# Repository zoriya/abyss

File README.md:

# Abyss

A 32 key split keyboard with a low pinky column.

## Components

| Count | Part name        | Size/Remark |
| :---: | :--------------  | :------ |
|   2x  | [Seeed Xiao nRF54L15 - mcu](https://www.seeedstudio.com/XIAO-nRF54L15-p-6493.html) | |
|   2x  | [1208YD - reset button](https://fr.aliexpress.com/item/1005003938985112.html?spm=a2g0o.order_list.order_list_main.5.21ef1802F8o6h5&gatewayAdapt=glo2fra) | 6x6x7mm |
|   2x  | [401030 Li-Po Battery](https://www.ebay.com/itm/171812433827) | 4x10x30mm |
|   2x  | [SM02B-SRSS-TB - battery connector](https://www.jst-mfg.com/product/pdf/eng/eSH.pdf) | |
|  32x  | choc switch | i use [sunsets](https://lowprokb.ca/products/sunset-tactile-choc-switches) |
|  30x  | 1u choc keycaps | i use [pom](https://splitkb.com/products/moergo-pom-mbk-profile-keycaps?variant=42898367152387) |
|   2x  | 1.5u choc keycaps | i use [pom](https://splitkb.com/products/moergo-pom-mbk-profile-keycaps?variant=42898363121923) |
|  32x  | [hotswap chock sockets](https://chosfox.com/products/kailh-choc-switch-1350-hot-swap-sockets?_pos=1&_sid=94423b5bb&_ss=r) | |
|  32x  | diodes | |
|  16x  | magnets | [20x8x1.5mm](https://www.amazon.fr/dp/B0DDCVJTG8?th=1) |
|   4x  | m2 screws | 4/6/8mm |
|   4x  | m2 standoff | [<5mm wide, 6mm height](https://www.aliexpress.us/item/3256804230166399.html?spm=a2g0o.productlist.main.6.3a56Op21Op215V&algo_pvid=0788da77-fa40-49b3-9d72-f4cf68a2b90f&algo_exp_id=0788da77-fa40-49b3-9d72-f4cf68a2b90f-5&pdp_ext_f=%7B%22order%22%3A%22229%22%2C%22eval%22%3A%221%22%7D&pdp_npi=6%40dis%21USD%212.35%210.99%21%21%212.35%210.99%21%40211b655217567292930196247e11b4%2112000029108517137%21sea%21US%210%21ABX%211%210%21n_tag%3A-29910%3Bd%3A8c8b81cd%3Bm03_new_user%3A-29895%3BpisId%3A5000000174221208&curPageLogUid=uw39hgxJul2o&utparam-url=scene%3Asearch%7Cquery_from%3A%7Cx_object_id%3A1005004416481151%7C_p_origin_prod%3A#nav-description)|

## Info

Case dimensions:
 - height: 10.5mm -> 1.6mm (pcb) + 3.1mm (hotswap socket) + 5.5mm (choc size on top of the pcb)
 - length: 115.38mm
 - width: 96.25mm

Transport case dimesions:
- height: 30mm (2x2mm for enclosure, 2x10.5mm for keyboard, 5mm in middle for keycaps + gap)
- length: 124.35mm
-  width: 105.25mm

## Keymap

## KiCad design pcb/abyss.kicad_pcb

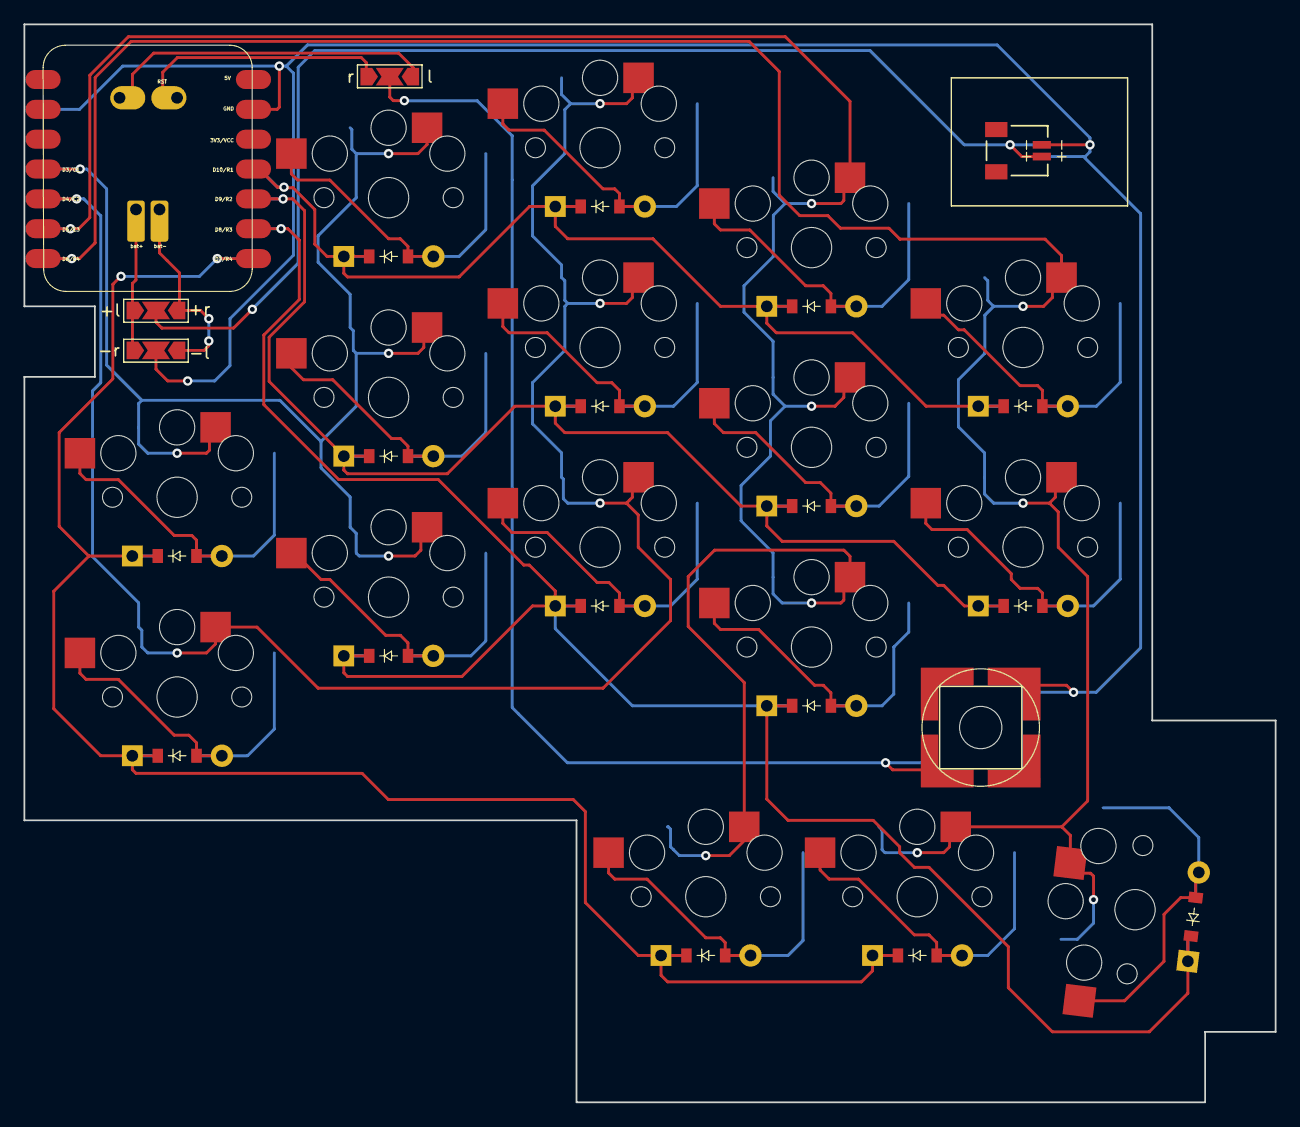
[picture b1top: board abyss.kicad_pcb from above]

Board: 2 copper layers, 106.5 x 91.8 mm, 32 parts (0 on the bottom side), 24 nets.

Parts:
D1, D2, D3, D4, D5, D6, D7, D8, D9, D10, D11, D12, D13, D14, D15, D16: ComboDiode
S1, S2, S3, S4, S5, S6, S7, S8, S9, S10, S11, S12, S13, S14, S15, S16: PG1350

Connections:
C1: S2.1, S3.1, S4.1, S5.1
C2: S1.1, S6.1, S7.1, S8.1
C3: S9.1, S10.1, S11.1, S14.1
C4: S12.1, S13.1, S15.1, S16.1
R1: D5.1, D8.1, D11.1, D13.1
R2: D4.1, D7.1, D10.1, D12.1
R3: D3.1, D6.1, D9.1, D16.1
R4: D1.1, D2.1, D14.1, D15.1
home_cluster: D15.2, S15.2
index_bottom: D9.2, S9.2
index_home: D10.2, S10.2
index_top: D11.2, S11.2
inner_bottom: D12.2, S12.2
inner_home: D13.2, S13.2
left_cluster: D14.2, S14.2
middle_bottom: D6.2, S6.2
middle_home: D7.2, S7.2
middle_top: D8.2, S8.2
pinky_bottom: D1.2, S1.2
pinky_home: D2.2, S2.2
right_cluster: D16.2, S16.2
ring_bottom: D3.2, S3.2
ring_home: D4.2, S4.2
ring_top: D5.2, S5.2

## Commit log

2024-01-31 Add outlines
2024-01-31 Add proper 1.5u thumb size
2024-01-31 Use higher padding
2024-02-04 Use square outlines and start pcb
2024-02-06 Add infused kim footprints
2024-02-06 Fix oled pos
2024-02-06 Add reset and power switch
2024-02-06 Rotate reset/power switches
2024-02-07 Add keys and oled routing hints
2024-02-07 Fix extra column in routing
2024-02-14 Fix nets
2024-02-15 Remove nice view footprint
2024-02-19 Add battery jst and cleanup layout
2024-02-19 Move jst connector at the top
2024-02-19 Add case walls
2024-02-20 Create plate
2024-02-20 Add mounting holes on the pcb
2024-02-20 Create top case
2024-02-20 Add mounting holes for the plate on the pcb
2024-02-20 Route pcb
2024-02-28 Finish pcb routing
2024-02-28 Add plate pcb
2024-03-17 Plate diffs
2024-04-07 Case wip
2024-04-07 Init zmk config
2024-04-07 Set github action working directory
2024-04-07 Override default config files names
2024-04-07 Create abyss shield
2024-04-07 Create basic keymap
2024-04-07 Move zmk config to root
2024-04-07 Add zmk metadata file
2024-04-07 Move boards to config foldre
2024-04-07 Move metadata file to boards/shield folder
2024-04-07 Add shield keymap
2024-04-07 Move back to config folder :(
2024-04-07 fix typo
2024-04-07 Remove zephyr module
2024-04-07 oups
2024-04-07 Rename dtsi to overlay
2024-04-07 Fix keymap
2024-04-07 Fix keymap codes
2024-04-08 Fix some keys
2024-04-10 Cleanup layout ascii art
2024-04-10 Add homerow mods
2024-04-10 Add missing keys as combo
2024-04-10 Add keymap draw tools
2024-04-10 Add home and end combo
2024-04-10 Add parenthesis combo
2024-04-10 Add dash/underscore combo
2024-04-10 Add symbols layer
2024-04-10 Fix bracket combo
2024-04-10 Add keymap.svg
2024-04-11 Add directions keys and esc combo
2024-04-11 Fix bscp and layout.svg
2024-04-11 Fix up/down swapped and space delay
2024-04-13 Add another z combo
2024-04-13 Add a : combo
2024-04-13 Add enter combo
2024-04-13 Add bluethooth bindings
2024-04-13 Change deep sleep timing to 20min
2024-04-13 Add media keys
2024-04-13 Add capswords
2024-04-13 Use play instead of playpause btn
2024-04-13 Use playpause instead of play
2024-04-15 Remove combo/mod require delay
2024-04-15 Fix weird nav keys
2024-04-15 Add a specefic enter key for shift enter
2024-04-30 Bind shift instead of enter on the left thumb
2024-04-30 Fix shift keycode
2024-04-30 Use urob fork to disable capsword after modifiers
2024-04-30 Add reset firmware to ci
2024-04-30 Use n0 on the two right thumbs
2024-05-22 Mark kscan as wakeup-source
2024-05-22 Use eager debouncing
2024-05-22 Enable split battery reporting
2024-07-14 Init FreeCad case project
2024-08-23 Define left/right keys instead of using them twice
2024-08-23 Add reset button
2024-08-23 Add reset on both sides
2024-08-23 Use my fork of zmk
2024-08-23 Fix reset
2024-09-12 Case top start
2024-09-12 Add mc pin holes
2024-09-13 Add walls and usb hole
2024-09-13 Add fillets
2024-09-13 Add inner fillets
2024-09-13 Add screw holes
2024-09-13 wip fix sketches
2024-09-13 fix sketches part 2
2024-09-14 wip wall part2
2024-09-14 Restart case and make clean sketches
2024-09-14 Correct sketches placements
2024-09-14 Create bottom lid
2024-09-14 Add screw holes in bottom lid
2024-09-15 things
2024-09-15 Make better bottom
2024-09-15 Better tolerances
2024-09-16 Add walls
2024-09-16 Add inner walls
2024-09-16 Correct inner wall
2024-09-16 Add screw holes in wall (part 1)
2024-09-17 Allign screw holes
2024-09-17 Fillet bottom walls
2024-09-17 Add key holes
2024-09-18 Add mc hole
2024-09-18 Better mc distances
2024-09-18 Add inner keys hole sketch
2024-09-18 Finish key hole sketch
2024-09-18 Add key hole
2024-09-18 Fix flipped constraints
2024-09-18 Fix recompute issues
2024-09-18 Add missing screw holes
2024-09-18 Add usb hole sketch
2024-09-18 Add usb hole
2024-09-19 Add nut holes
2024-09-19 Remove corners for nut holes
2024-09-22 Add feet holes
2024-09-23 Add feets
2024-09-23 Remove old case tries
2024-09-27 Draft feets
2024-09-27 Make nut slot smaller
2024-09-27 Update orchidee.svg to real svg
2024-09-27 Remake lid
2024-09-27 Properly allign screw holes
2024-09-29 Add nut shape in holes
2024-09-29 new orchid
2024-09-29 Add the orchid on the surface
2024-09-29 Add tolerence for feets
2024-09-29 Fix spacing
2024-09-30 Remove bottom ledge & increment lit tolerence
2024-09-30 Reduce wall height
2024-09-30 Increment feet tolerences & height
2024-10-01 Fix feet magnet pocket height
2024-10-01 Widen screw holes
2024-10-01 Reset orchid drawing (source from flora)
2024-10-01 Scale orchid by 1.1 & flip horizontally
2024-10-01 Scale orchid path
2024-10-03 Add nut slot covers
2024-10-03 Update orchid
2024-10-03 Add slots for nuts
2024-10-06 Fix lid tolerences and rework nut slot
2024-10-14 Add keep mod shift for arrows
2024-10-14 Add hold shift on capsword
2024-10-15 Fix arrows
2024-12-06 Add keymap-drawer to shell.nix
2024-12-06 Add require delay to homerow mods
2024-12-06 Swap capsword w/ sticky lshift
2024-12-06 Configure sticky shift to be good
2025-01-19 Remove useless z combo
2025-02-09 Add shift on left hand
2025-02-09 Update keymap drawer
2025-02-09 Fix caps_word not working due to zmkfirmware/zmk#834
2025-02-09 Disable sticky shift lazy
2025-02-25 Handle caps word cancellation
2025-04-13 Start rework
2025-04-13 Add xiao footprint
2025-04-13 Fix mcu position
2025-04-13 Reverse battery connector
2025-04-13 Remove pcb
2025-04-13 Init pcb & add mcu
2025-04-14 Add power switch footprint
2025-04-17 Restart case
2025-04-18 Re-rework case
2025-04-18 Move case2 to case
2025-04-18 Add key cutout
2025-04-18 Try to fix distances
2025-04-18 Fix thumb key
2025-04-18 Add battery slot
2025-08-17 Fix case height
2025-08-17 Fix tolerences
2025-08-18 Add socket holes
2025-08-18 Move usb hole to bottom
2025-08-18 wip: Create transport case
2025-08-18 Add honeycomb for case
2025-08-18 Open case in two
2025-08-18 Add case stands
2025-08-18 Start feet slips
2025-08-19 Add feet slips on case
2025-08-19 Pad case to fit keyboard correctly
2025-08-20 Fix socket hole
2025-08-20 Add m2 holes to fix bottom & top
2025-08-20 Make case more square
2025-08-20 Add case side stands
2025-08-20 Fix pcb size
2025-08-20 Fix transport case cuttout
2025-08-20 Transport case gap
2025-08-20 Reinit pcb
2025-08-25 wip: Add mc footprint
2025-08-25 wip: Fix case angle
2025-08-26 Fix case angle
2025-08-26 Cleanup case
2025-08-26 Use 4mm walls for transport case
2025-08-26 wip: Better case
2025-08-26 wip: Pcb
2025-08-26 Fix angles
2025-08-26 Cleanup fillets
2025-08-26 Add magnet holes
2025-08-26 Add reset button hole
2025-08-26 Add reset button to pcb
2025-08-26 Add through hole for reset btn
2025-08-26 Add counterbore for m2
2025-08-26 wip: Add m2 holes in pcb
2025-08-30 Use ergogen and keymap-drawer from nixpkgs now that they are packaged
2025-08-30 Cleanup footprints
2025-08-30 Fix row/column net in ergogen
2025-08-30 Start to name nets
2025-08-30 Fix netnames of all keys
2025-08-31 Route gnd & 5v
2025-08-31 Route most keys
2025-08-31 Route everything
2025-08-31 Remove usb cutout
2025-08-31 Move magnets
2025-08-31 Move magnets in case
2025-08-31 Center magnet in case stand
2025-08-31 wip: Add stand magnets holes
2025-08-31 Cleanup material list
2025-09-01 Remake m2 standoff holes
2025-09-01 Add second m2 standoff
2025-09-01 Move m2 holes in bottom lid
2025-09-03 Add tri jumper
2025-09-03 Fix warnings
2025-09-04 Finish pcb
2025-09-18 Fix some case issues
2025-09-18 Fix magnet hole placements
2025-09-18 Angle slit
2025-09-20 Fix m2 holes and standoff
2025-09-20 Fix case size
2025-09-20 Fix usb hole placement
2025-09-21 Fix key position
2025-09-21 Fix holes in top
2025-09-22 Fix magnets in case
2025-10-26 Cleanup mc hole & magnet holes
2025-10-26 Fix rst btn
2025-10-29 wip: Battery and mc fixes
2025-11-04 Add pcb tri jumper for reset
2025-11-04 Fix case
2025-11-07 Fix resetbtn & bat conn
2025-11-07 Use reflow for mc
2026-01-23 Use xiao ble
2026-01-24 Use new config format
2026-02-21 Update boards definition
2026-02-24 coucouaa e e e e J: Change ID: yzmnspou
2026-02-24 Fix usb
2026-02-24 Fix some stuff
2026-02-26 Fix usb + holes
2026-02-26 Fix case magnets
2026-02-26 Fix stand magnets
2026-02-26 Fix case position
2026-02-26 Cleanup
2026-02-27 Band holder
2026-02-27 Band slider
2026-02-27 Cleanup band holder
2026-02-27 Finish holder
2026-02-28 Magnet try 2
2026-02-28 Continue magnets
2026-02-28 Triple magnet on each side
2026-02-28 Add mirrored bottom
2026-03-01 Bottom right
2026-03-01 Remove third magnet
2026-03-01 Remove thrid magnet in case
2026-03-01 Remove band holder
2026-03-02 Configure capslock
2026-03-02 Move capsword to combo
2026-03-02 Shift capslock to handle esc remap
